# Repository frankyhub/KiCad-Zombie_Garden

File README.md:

<div align="center">

|[:skull:ISSUE](https://github.com/frankyhub/KiCad-Zombie_Garden/issues?q=is%3Aissue)|[:speech_balloon: Forum /Discussion](https://github.com/frankyhub/KiCad-Zombie_Garden/discussions)|[:grey_question:WiKi](https://github.com/frankyhub/KiCad-Zombie_Garden/wiki)||
|--|--|--|--|
| | | | |
<a href="https://github.com/frankyhub/KiCad-Zombie_Garden/issues">|<a href="https://github.com/frankyhub/KiCad-Zombie_Garden/discussions">|<a href="https://github.com/frankyhub/KiCad-Zombie_Garden/releases">||
|| <a href="https://github.com/frankyhub/KiCad-Zombie_Garden/pulse" alt="Activity">| <a href="https://github.com/frankyhub/KiCad-Zombie_Garden/graphs/traffic">  |<a href="https://github.com/frankyhub?tab=stars"> ||

</div>

# KiCad-Zombie_Garden
My ugly backlight Zombies

### May I introduce:

### Bruce

### Freddie

### Kylie

### Tucker

### Nicki

### Carlos

### Kathi

### Eddie

---

---

<div style="position:absolute; left:2cm; ">   
<ol class="breadcrumb" style="border-top: 2px solid black;border-bottom:2px solid black; height: 45px; width: 900px;"> <p align="center"><a href="#oben">nach oben</a></p></ol>
</div>  

---

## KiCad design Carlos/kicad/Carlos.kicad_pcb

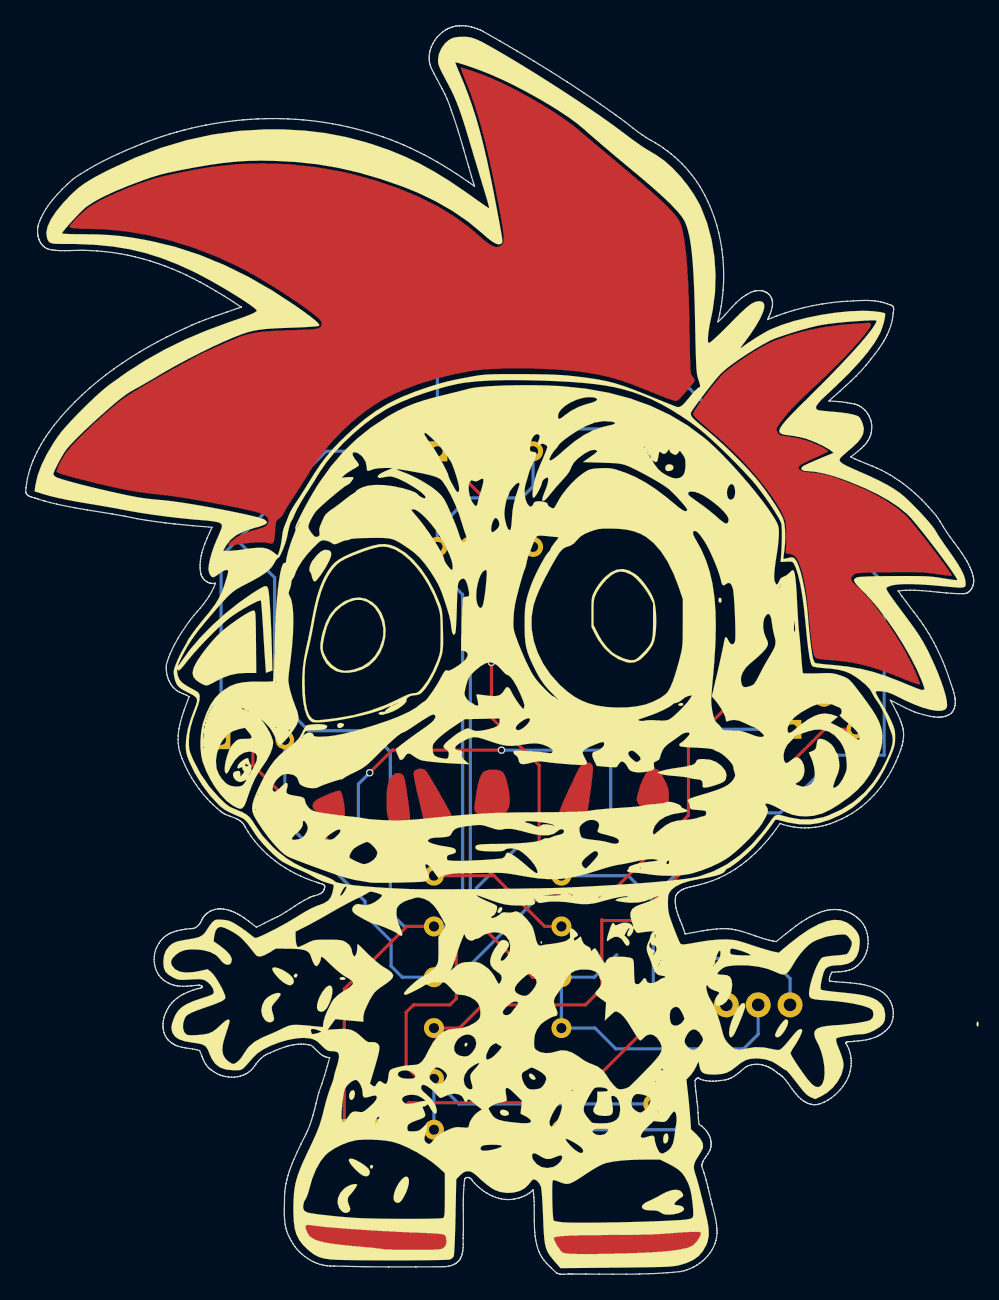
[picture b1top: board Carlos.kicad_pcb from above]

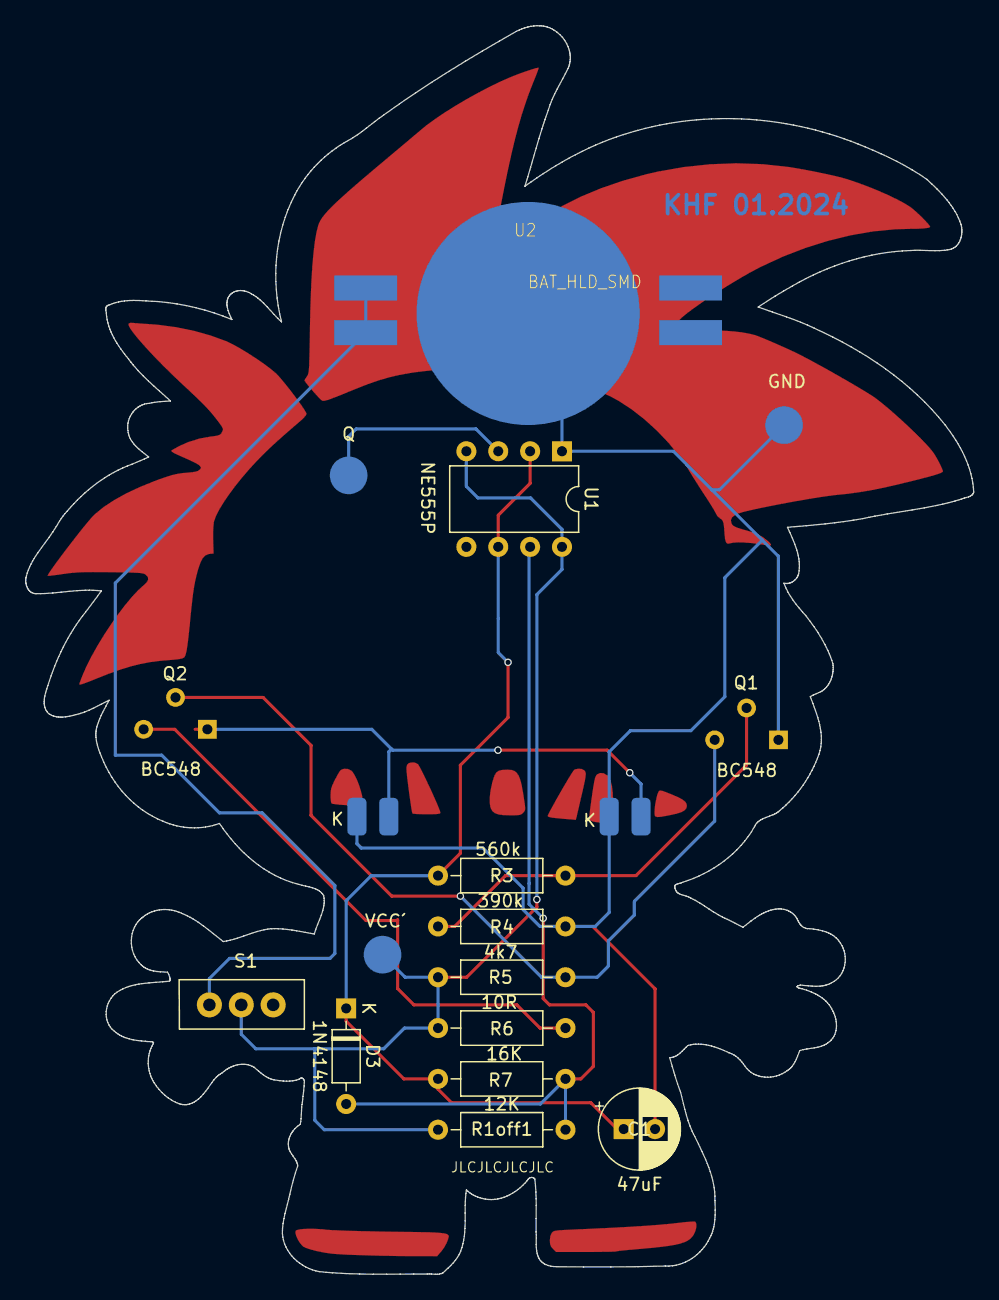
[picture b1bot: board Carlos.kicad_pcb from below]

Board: 2 copper layers, 75.6 x 99.5 mm, 16 parts (14 on the bottom side), 9 nets.

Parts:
C1: 47uF; CP_Radial_D6.3mm_P2.50mm
D3: 1N4148; D_DO-35_SOD27_P7.62mm_Horizontal
K: LED; LED-Eule
K#2: LED; LED-Eule
Q: LP_rund
Q1, Q2: Q_NPN_EBC; TO-92L_Wide
R1off1: 12K; R_Axial_DIN0207_L6.3mm_D2.5mm_P10.16mm_Horizontal
R3: 560k; R_Axial_DIN0207_L6.3mm_D2.5mm_P10.16mm_Horizontal
R4: 390k; R_Axial_DIN0207_L6.3mm_D2.5mm_P10.16mm_Horizontal
R5: 4k7; R_Axial_DIN0207_L6.3mm_D2.5mm_P10.16mm_Horizontal
R6: 10R; R_Axial_DIN0207_L6.3mm_D2.5mm_P10.16mm_Horizontal
R7: 16K; R_Axial_DIN0207_L6.3mm_D2.5mm_P10.16mm_Horizontal
S1: Micro_Schalter; Micro_SchalterKHF
U1: NE555P; DIP-8_W7.62mm
U2: BAT_HLD_SMD; BAT-HLD-SMD-Blech

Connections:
unnamed: K.2 (A), K#2.2 (A), Q2.1 (E)
unnamed: C1.2, K.1 (K), K#2.1 (K), Q1.1 (E), R4.2, U1.1 (GND), U2.2
unnamed: D3.2 (A), R1off1.2, R7.2, U1.7 (DIS)
unnamed: C1.1, D3.1 (K), R3.1, R7.1, U1.2 (TR), U1.6 (THR)
unnamed: Q1.2 (B), R3.2, R4.1
unnamed: Q1.3 (C), Q2.2 (B), R5.2
unnamed: Q2.3 (C), R6.2
unnamed: S1.1 (A), U2.1
unnamed: R1off1.1, R5.1, R6.1, S1.2 (E), U1.4 (R), U1.8 (VCC)

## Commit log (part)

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2024-02-23 23-02-2024
2024-10-12 V12102024
